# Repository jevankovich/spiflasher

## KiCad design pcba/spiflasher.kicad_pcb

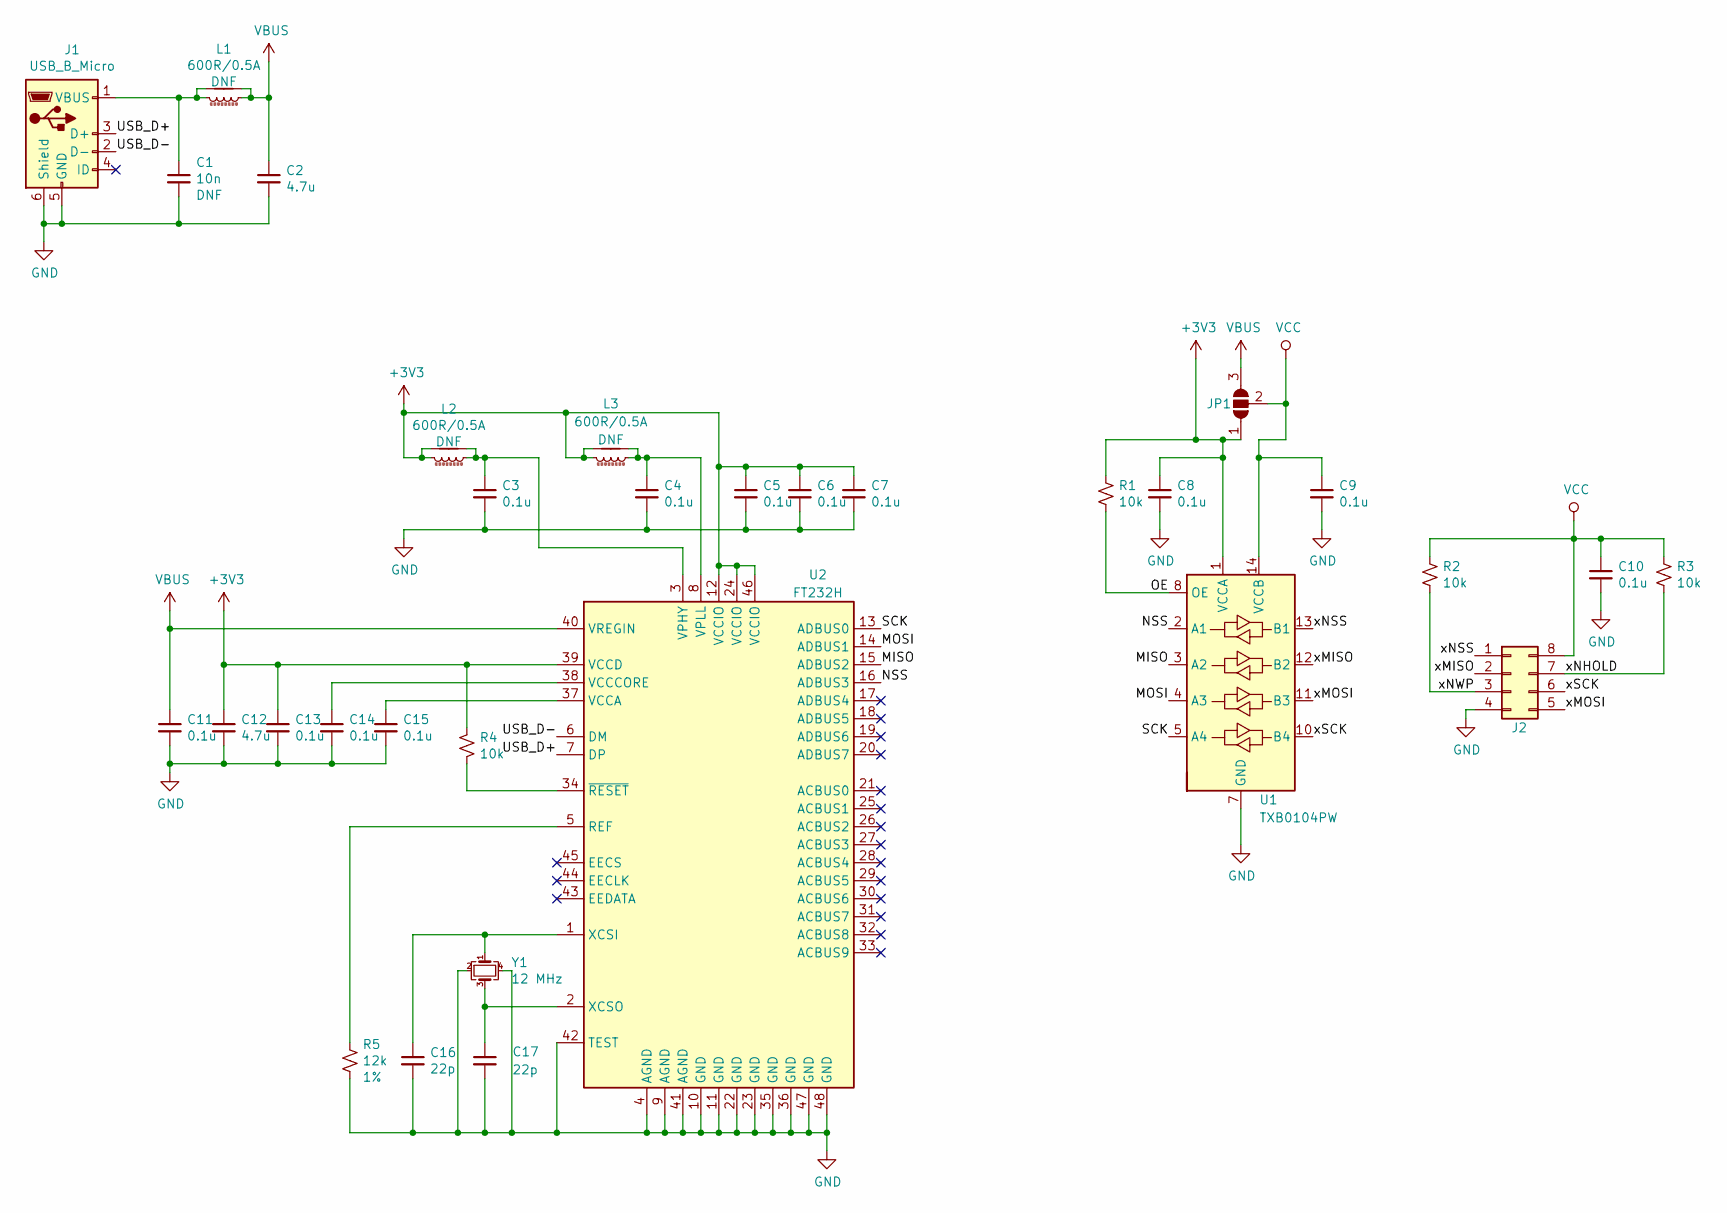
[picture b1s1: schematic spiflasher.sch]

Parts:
C1: 10n; C_0603_1608Metric; LCSC C57112
C2, C12: 4.7u; C_0603_1608Metric; LCSC C19666
C3, C4, C5, C6, C7, C11, C13, C14, C15: 0.1u; C_0402_1005Metric; LCSC C1525
C8, C9, C10: 0.1u; C_0603_1608Metric; LCSC C14663
C16, C17: 22p; C_0603_1608Metric; LCSC C1653
J1: USB_B_Micro; USB_Micro-B_GCT_USB3070; Digikey 2073-USB3070-30-ACT-ND
J2: Conn_02x04_Counter_Clockwise; DIP-8_W7.62mm_Socket; Digikey 1212-1003-ND
JP1: SolderJumper_3_Open; SolderJumper-3_P1.3mm_Open_RoundedPad1.0x1.5mm_NumberLabels
L1, L2, L3: 600R/0.5A; L_0603_1608Metric; LCSC C21189
NT1, NT2, NT3: Net-Tie_2; NetTie-2_SMD_Pad0.5mm
R1, R2, R3, R4: 10k; R_0603_1608Metric; LCSC C25804
R5: 12k; R_0603_1608Metric; Tolerance 1%; LCSC C22790
U1: TXB0104PW; TSSOP-14_4.4x5mm_P0.65mm; LCSC C60708
U2: FT232H; LQFP-48_7x7mm_P0.5mm; LCSC C51997
Y1: 12 MHz; Crystal_SMD_3225-4Pin_3.2x2.5mm; LCSC C9002

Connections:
+3V3: C5.1, C6.1, C7.1, C8.1, C12.1, C13.1, JP1.1 (A), L2.2, L3.2, NT2.1, NT3.1, R1.1, R4.1, U1.1 (VCCA), U2.12 (VCCIO), U2.24 (VCCIO), U2.39 (VCCD), U2.46 (VCCIO)
/MISO: U1.3 (A2), U2.15 (ADBUS2)
/MOSI: U1.4 (A3), U2.14 (ADBUS1)
/NSS: U1.2 (A1), U2.16 (ADBUS3)
/OE: R1.2, U1.8 (OE)
/SCK: U1.5 (A4), U2.13 (ADBUS0)
/USB_D+: J1.3 (D+), U2.7 (DP)
/USB_D-: J1.2 (D-), U2.6 (DM)
/xMISO: J2.2, U1.12 (B2)
/xMOSI: J2.5, U1.11 (B3)
/xNHOLD: J2.7, R3.2
/xNSS: J2.1, U1.13 (B1)
/xNWP: J2.3, R2.2
/xSCK: J2.6, U1.10 (B4)
GND: C1.2, C2.2, C3.2, C4.2, C5.2, C6.2, C7.2, C8.2, C9.2, C10.2, C11.2, C12.2, C13.2, C14.2, C15.2, C16.2, C17.2, J1.5 (GND), J1.6 (Shield), J2.4, R5.2, U1.7 (GND), U2.4 (AGND), U2.9 (AGND), U2.10 (GND), U2.11 (GND), U2.22 (GND), U2.23 (GND), U2.35 (GND), U2.36 (GND), U2.41 (AGND), U2.42 (TEST), U2.47 (GND), U2.48 (GND), Y1.2, Y1.4
unnamed: C1.1, J1.1 (VBUS), L1.2, NT1.1
unnamed: C3.1, L2.1, NT2.2, U2.3 (VPHY)
unnamed: C4.1, L3.1, NT3.2, U2.8 (VPLL)
unnamed: C14.1, U2.38 (VCCCORE)
unnamed: C15.1, U2.37 (VCCA)
unnamed: C16.1, U2.1 (XCSI), Y1.1
unnamed: C17.1, U2.2 (XCSO), Y1.3
unnamed: R4.2, U2.34 (~RESET)
unnamed: R5.1, U2.5 (REF)
VBUS: C2.1, C11.1, JP1.3 (B), L1.1, NT1.2, U2.40 (VREGIN)
VCC: C9.1, C10.1, J2.8, JP1.2 (C), R2.1, R3.1, U1.14 (VCCB)

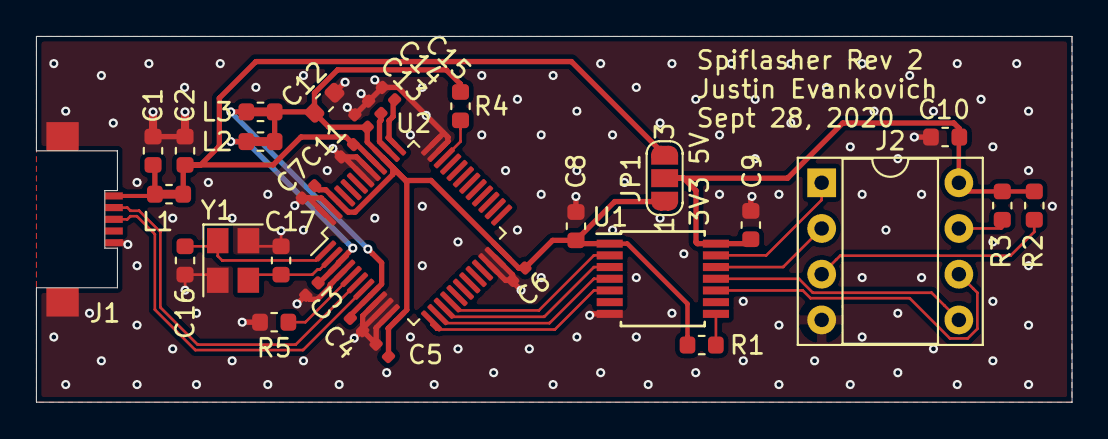
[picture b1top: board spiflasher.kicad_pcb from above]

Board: 2 copper layers, 57.5 x 20.3 mm, 34 parts (0 on the bottom side), 26 nets.

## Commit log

2020-08-30 Added bom generation
2020-08-30 more gitifnore
2020-09-02 Changed crystal Digikey P/N to a non-marketplace one
2020-09-09 Removed unnecessary components.
2020-09-27 Uncertain
2020-09-28 Low profile USB port. Final Rev 2
2020-09-30 Added 3D model for USB port
2020-10-01 Create LICENSE
2020-12-01 Create main.yml
    Trying github actions
2020-12-01 Update main.yml
    Point to github mirror of flashrom
2020-12-01 Update main.yml
    Should create a new github release when run
2020-12-01 Update main.yml
    Should fix some issues
2020-12-01 Update main.yml
    Added caching and fixed typos
2020-12-01 Update main.yml
    Should fix issue with creating release
2020-12-01 Update main.yml
    Upload artifact instead of release
2020-12-01 Update main.yml
    Fix nested zips
2020-12-01 Update main.yml
    cache .exe instead of .zip
2020-12-01 Update main.yml
    Copy dlls instead of guessing at paths
2020-12-01 Update main.yml
    Fix paths
